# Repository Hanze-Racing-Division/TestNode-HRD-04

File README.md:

# TestNode-HRD-04
Decentralised measurement units

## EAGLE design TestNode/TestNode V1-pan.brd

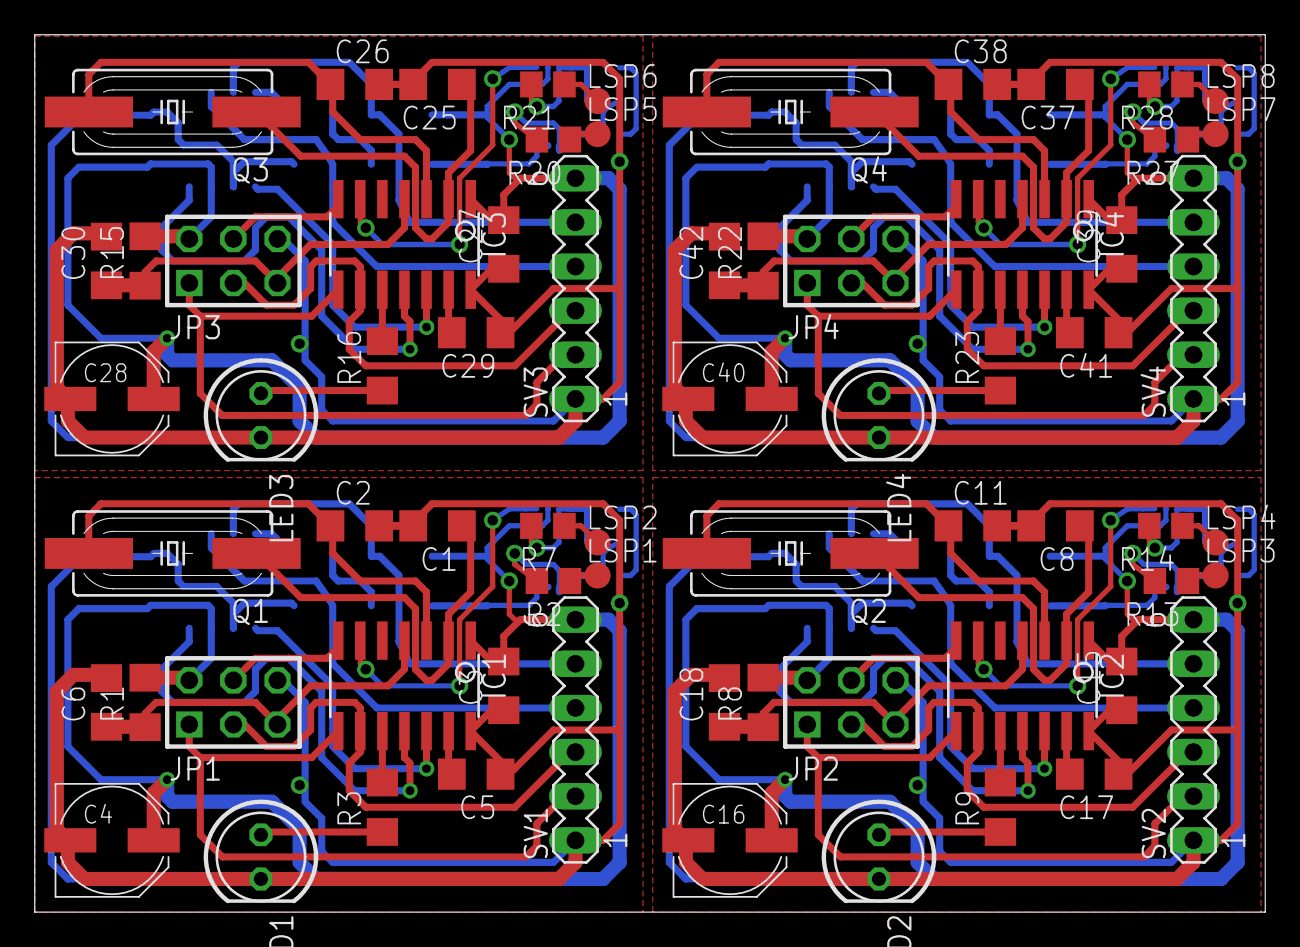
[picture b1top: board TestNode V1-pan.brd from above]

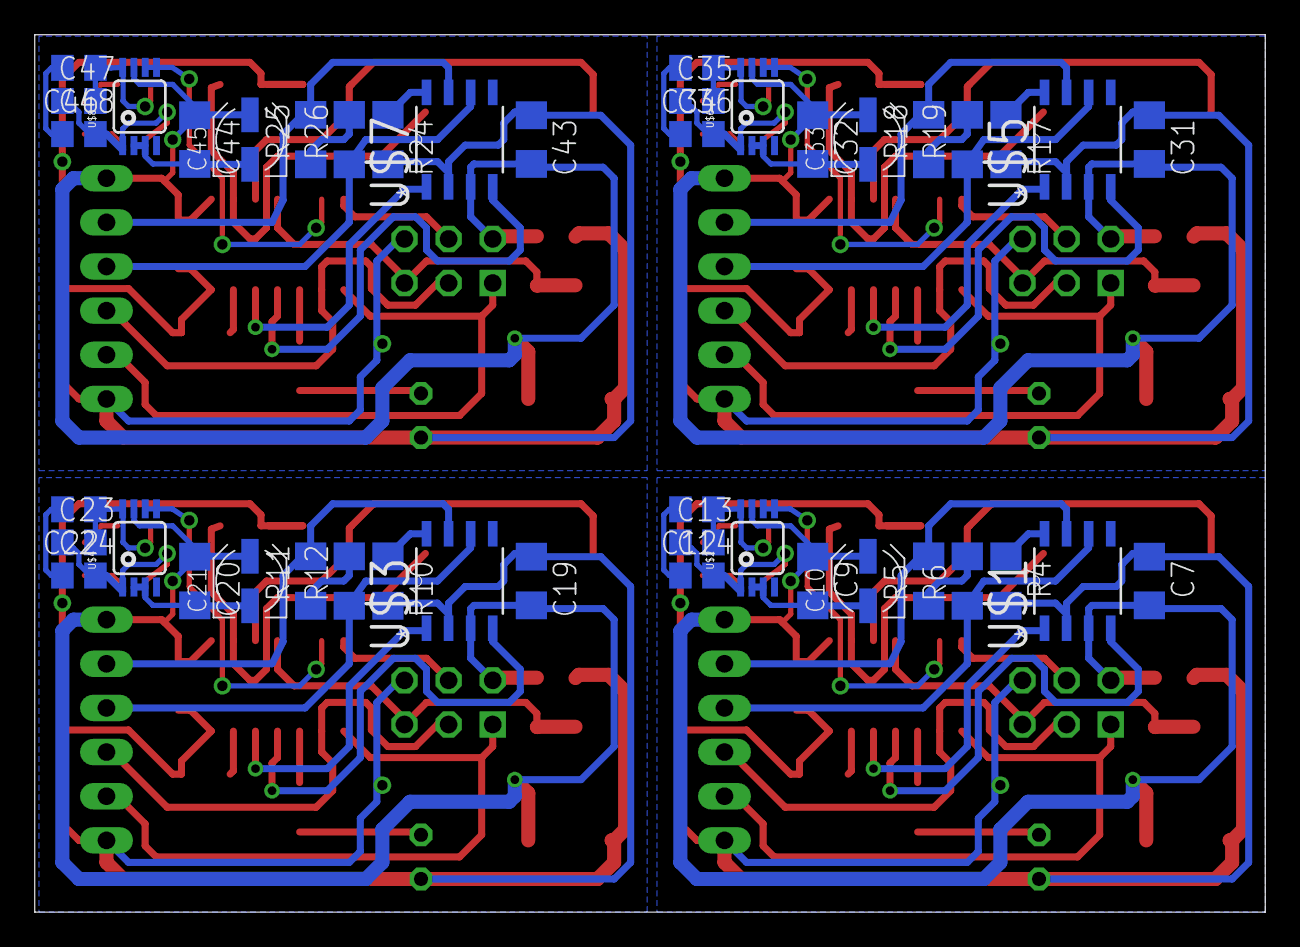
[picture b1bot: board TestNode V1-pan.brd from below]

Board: 2 copper layers, 70.8 x 50.5 mm, 112 parts (44 on the bottom side), 88 nets.

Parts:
C1, C2, C6, C8, C11, C18, C25, C26, C30, C37, C38, C42: 22pF; C1206
C3, C5, C7, C9, C15, C17, C19, C20, C27, C29, C31, C32, C39, C41, C43, C44: 100nF; C1206
C4, C16, C28, C40: 100uF; PANASONIC_D
C10, C21, C33, C45: 10uF; UD-4X5,8_NICHICON
C12, C13, C14, C22, C23, C24, C34, C35, C36, C46, C47, C48: 100nF; C0805
IC1, IC2, IC3, IC4: TINY24/44/84-SSU; SOIC14
JP1, JP2, JP3, JP4: AVR-ISP-6VERT; AVR-ISP-6
LED1, LED2, LED3, LED4: LED5MM
LSP1, LSP2, LSP3, LSP4, LSP5, LSP6, LSP7, LSP8: TPTP15R; TP15R
Q1, Q2, Q3, Q4: 16Mhz; SM49
R1, R4, R8, R10, R15, R17, R22, R24: 10k; R1206
R2, R7, R13, R14, R20, R21, R27, R28: 1k; R0805
R3, R9, R16, R23: 470; R1206
R5, R11, R18, R25: 120; R1206
R6, R12, R19, R26: 0; R1206
SV1, SV2, SV3, SV4: MA06-1
U$1, U$3, U$5, U$7: MCP2551-I/SN; SOIC127P600X175-8N
U$2, U$4, U$6, U$8: AD849X; MSOP8

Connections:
ADC1: IC2.10, R9.2
ADC2: IC2.6, U$4.5, U$4.6
ADC3: IC1.10, R3.2
ADC4: IC3.10, R16.2
ADC5: IC3.6, U$6.5, U$6.6
ADC6: IC4.10, R23.2
ADC7: IC1.6, U$2.5, U$2.6
ADC8: IC4.6, U$8.5, U$8.6
GND: C1.2, C2.2, C3.1, C4.-, C5.1, C6.2, C7.1, C9.2, C10.-, C12.2, C14.1, IC1.14, JP1.6, LED1.K, R4.2, SV1.1, U$1.2, U$2.2, U$2.3
GND1: C8.2, C11.2, C15.1, C16.-, C17.1, C18.2, C19.1, C20.2, C21.-, C22.2, C24.1, IC2.14, JP2.6, LED2.K, R10.2, SV2.1, U$3.2, U$4.2, U$4.3
GND2: C25.2, C26.2, C27.1, C28.-, C29.1, C30.2, C31.1, C32.2, C33.-, C34.2, C36.1, IC3.14, JP3.6, LED3.K, R17.2, SV3.1, U$5.2, U$6.2, U$6.3
GND3: C37.2, C38.2, C39.1, C40.-, C41.1, C42.2, C43.1, C44.2, C45.-, C46.2, C48.1, IC4.14, JP4.6, LED4.K, R24.2, SV4.1, U$7.2, U$8.2, U$8.3
MISO: IC1.8, JP1.1, SV1.2
MISO1: IC2.8, JP2.1, SV2.2
MISO2: IC3.8, JP3.1, SV3.2
MISO3: IC4.8, JP4.1, SV4.2
MOSI: IC1.7, JP1.4
MOSI1: IC2.7, JP2.4
MOSI2: IC3.7, JP3.4
MOSI3: IC4.7, JP4.4
unnamed: C1.1, IC1.2, Q1.1
unnamed: C2.1, IC1.3, Q1.2
unnamed: C12.1, C13.2, R7.2, U$2.8
unnamed: C5.2, IC1.13
unnamed: R4.1, U$1.8
unnamed: LED1.A, R3.1
unnamed: R5.1, R6.2
unnamed: C13.1, C14.2, R2.2, U$2.1
unnamed: C8.1, IC2.2, Q2.1
unnamed: LSP1.TP, R2.1
unnamed: LSP2.TP, R7.1
unnamed: C11.1, IC2.3, Q2.2
unnamed: C17.2, IC2.13
unnamed: LED2.A, R9.1
unnamed: R10.1, U$3.8
unnamed: R11.1, R12.2
unnamed: C22.1, C23.2, R14.2, U$4.8
unnamed: C23.1, C24.2, R13.2, U$4.1
unnamed: LSP3.TP, R13.1
unnamed: LSP4.TP, R14.1
unnamed: C25.1, IC3.2, Q3.1
unnamed: C26.1, IC3.3, Q3.2
unnamed: C29.2, IC3.13
unnamed: LED3.A, R16.1
unnamed: R17.1, U$5.8
unnamed: R18.1, R19.2
unnamed: C34.1, C35.2, R21.2, U$6.8
unnamed: C35.1, C36.2, R20.2, U$6.1
unnamed: LSP5.TP, R20.1
unnamed: LSP6.TP, R21.1
unnamed: C37.1, IC4.2, Q4.1
unnamed: C38.1, IC4.3, Q4.2
unnamed: C41.2, IC4.13
unnamed: LED4.A, R23.1
unnamed: R24.1, U$7.8
unnamed: R25.1, R26.2
unnamed: C46.1, C47.2, R28.2, U$8.8
unnamed: C47.1, C48.2, R27.2, U$8.1
unnamed: LSP7.TP, R27.1
unnamed: LSP8.TP, R28.1
RST: C6.1, IC1.4, JP1.5, R1.1
RST1: C18.1, IC2.4, JP2.5, R8.1
RST2: C30.1, IC3.4, JP3.5, R15.1
RST3: C42.1, IC4.4, JP4.5, R22.1
RX0: IC1.11, U$1.4
RX1: IC2.11, U$3.4
RX2: IC3.11, U$5.4
RX3: IC4.11, U$7.4
SCK: IC1.9, JP1.3, SV1.3
SCK1: IC2.9, JP2.3, SV2.3
SCK2: IC3.9, JP3.3, SV3.3
SCK3: IC4.9, JP4.3, SV4.3
TX0: IC1.12, U$1.1
TX1: IC2.12, U$3.1
TX2: IC3.12, U$5.1
TX3: IC4.12, U$7.1
UART0+: R5.2, SV1.5, U$1.7
UART0+1: R11.2, SV2.5, U$3.7
UART0+2: R18.2, SV3.5, U$5.7
UART0+3: R25.2, SV4.5, U$7.7
UART0-: R6.1, SV1.4, U$1.6
UART0-1: R12.1, SV2.4, U$3.6
UART0-2: R19.1, SV3.4, U$5.6
UART0-3: R26.1, SV4.4, U$7.6
VCC: C3.2, C4.+, C7.2, C9.1, C10.+, IC1.1, JP1.2, R1.2, SV1.6, U$1.3, U$2.7
VCC1: C15.2, C16.+, C19.2, C20.1, C21.+, IC2.1, JP2.2, R8.2, SV2.6, U$3.3, U$4.7
VCC2: C27.2, C28.+, C31.2, C32.1, C33.+, IC3.1, JP3.2, R15.2, SV3.6, U$5.3, U$6.7
VCC3: C39.2, C40.+, C43.2, C44.1, C45.+, IC4.1, JP4.2, R22.2, SV4.6, U$7.3, U$8.7

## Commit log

2016-04-21 added eagle files
